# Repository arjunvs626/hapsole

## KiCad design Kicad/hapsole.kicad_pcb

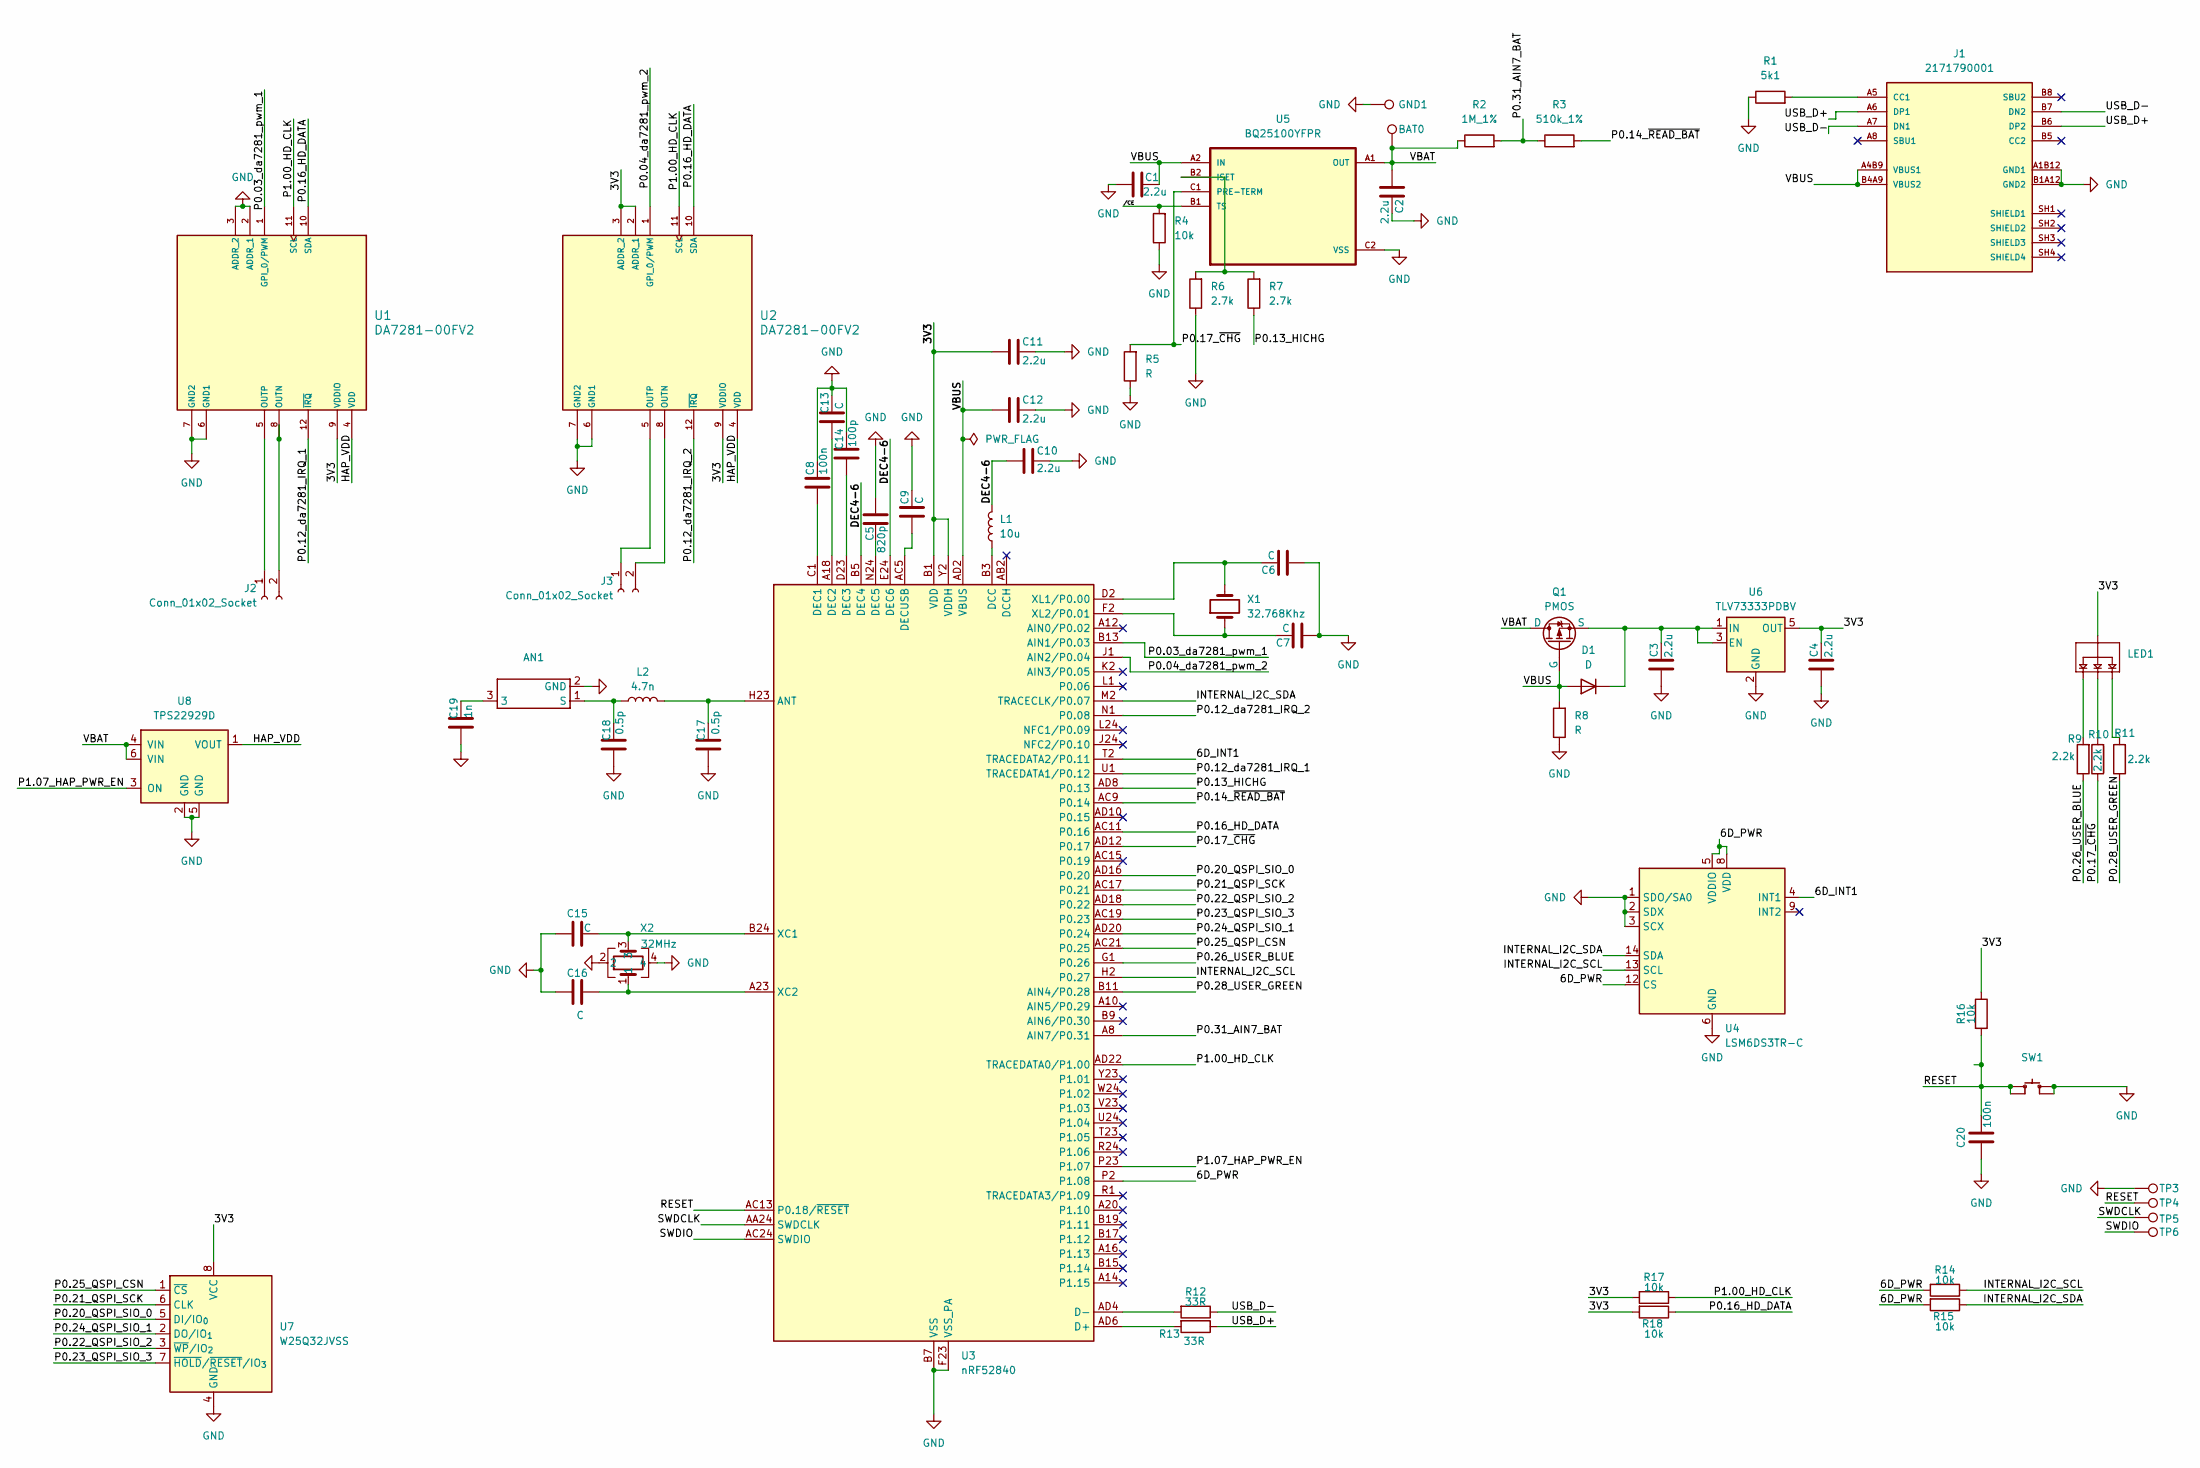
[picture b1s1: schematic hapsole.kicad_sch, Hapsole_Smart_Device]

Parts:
AN1: ANT
C1, C2, C3, C4, C10, C11, C12: 2.2u; C_0201_0603Metric
C5: 820p; C_0201_0603Metric
C6, C7, C9, C13, C15, C16: C; C_0201_0603Metric
C8, C20: 100n; C_0201_0603Metric
C14: 100p; C_0201_0603Metric
C17, C18: 0.5p; C_0201_0603Metric
C19: 1n; C_0201_0603Metric
D1: D; D_0603_1608Metric
J1: 2171790001; MOLEX_2171790001; PARTREV A1; DigiKey_Part_Number 900-2171790001CT-ND
J2, J3: Conn_01x02_Socket; JST_S2B-ZR-SM4A-TF
L1: 10u; L_0402_1005Metric
L2: 4.7n; L_0402_1005Metric
LED1: RGB_LED
Q1: PMOS; SOT-883
R1: 5k1; R_0201_0603Metric
R2: 1M_1%; R_0201_0603Metric
R3: 510k_1%; R_0201_0603Metric
R4, R14, R15, R16, R17, R18: 10k; R_0201_0603Metric
R5, R8: R; R_0201_0603Metric
R6, R7: 2.7k; R_0201_0603Metric
R9, R10, R11: 2.2k; R_0201_0603Metric
R12, R13: 33R; R_0201_0603Metric
SW1: DPST
TP1: BAT0; TestPoint_Pad_D1.5mm
TP2: GND1; TestPoint_Pad_D1.5mm
TP3, TP4, TP5, TP6: TestPoint; TestPoint_Pad_1.0x1.0mm
U1, U2: DA7281-00FV2; DA7281-00FV2_DIL
U3: nRF52840; Nordic_AQFN-73-1EP_7x7mm_P0.5mm
U4: LSM6DS3TR-C; LGA-14_3x2.5mm_P0.5mm_LayoutBorder3x4y
U5: BQ25100YFPR; BGA6N40P3X2_157X88X50N
U6: TLV73333PDBV; SOT-23-5
U7: W25Q32JVSS; Untitled
U8: TPS22929D; SOT-23-6
X1: 32.768Khz; FC135
X2: 32MHz; XC

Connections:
/3V3: C4.2, C11.1, LED1.+, R16.1, R17.2, R18.2, U1.9 (VDDIO), U2.2 (ADDR_1), U2.3 (ADDR_2), U2.9 (VDDIO), U3.A22 (VDD), U3.AD14 (VDD), U3.AD23 (VDD), U3.B1 (VDD), U3.W1 (VDD), U3.Y2 (VDDH), U6.5 (OUT), U7.8 (VCC)
/6D_INT1: U3.T2 (TRACEDATA2/P0.11), U4.4 (INT1)
/6D_PWR: R14.2, R15.2, U3.P2 (P1.08), U4.5 (VDDIO), U4.8 (VDD), U4.12 (CS)
/DEC4-6: C10.1, L1.2, U3.B5 (DEC4), U3.E24 (DEC6)
/HAP_VDD: U1.4 (VDD), U2.4 (VDD), U8.1 (VOUT)
/INTERNAL_I2C_SCL: R14.1, U3.H2 (P0.27), U4.13 (SCL)
/INTERNAL_I2C_SDA: R15.1, U3.M2 (TRACECLK/P0.07), U4.14 (SDA)
/P0.03_da7281_pwm_1: U1.1 (GPI_0/PWM), U3.B13 (AIN1/P0.03)
/P0.04_da7281_pwm_2: U2.1 (GPI_0/PWM), U3.J1 (AIN2/P0.04)
/P0.12_da7281_IRQ_1: U1.12 (~IRQ), U3.U1 (TRACEDATA1/P0.12)
/P0.12_da7281_IRQ_2: U2.12 (~IRQ), U3.N1 (P0.08)
/P0.13_HICHG: R7.1, U3.AD8 (P0.13)
/P0.14_~READ_BAT: R3.2, U3.AC9 (P0.14)
/P0.16_HD_DATA: R18.1, U1.10 (SDA), U2.10 (SDA), U3.AC11 (P0.16)
/P0.17_~CHG: R5.2, R10.1, U3.AD12 (P0.17), U5.C1 (PRE-TERM)
/P0.20_QSPI_SIO_0: U3.AD16 (P0.20), U7.5 (DI/IO_{0})
/P0.21_QSPI_SCK: U3.AC17 (P0.21), U7.6 (CLK)
/P0.22_QSPI_SIO_2: U3.AD18 (P0.22), U7.3 (~WP/IO_{2})
/P0.23_QSPI_SIO_3: U3.AC19 (P0.23), U7.7 (~HOLD/~RESET/IO_{3})
/P0.24_QSPI_SIO_1: U3.AD20 (P0.24), U7.2 (DO/IO_{1})
/P0.25_QSPI_CSN: U3.AC21 (P0.25), U7.1 (~CS)
/P0.26_USER_BLUE: R9.1, U3.G1 (P0.26)
/P0.28_USER_GREEN: R11.1, U3.B11 (AIN4/P0.28)
/P0.31_AIN7_BAT: R2.2, R3.1, U3.A8 (AIN7/P0.31)
/P1.00_HD_CLK: R17.1, U1.11 (SCL), U2.11 (SCL), U3.AD22 (TRACEDATA0/P1.00)
/P1.07_HAP_PWR_EN: U3.P23 (P1.07), U8.3 (ON)
/RESET: C20.1, R16.2, SW1.1 (A0), SW1.3 (A1), TP4.1, U3.AC13 (P0.18/~RESET)
/SWDCLK: TP5.1, U3.AA24 (SWDCLK)
/SWDIO: TP6.1, U3.AC24 (SWDIO)
/USB_D+: J1.A6 (DP1), J1.B6 (DP2), R13.1
/USB_D-: J1.A7 (DN1), J1.B7 (DN2), R12.1
/VBAT: C2.1, Q1.1 (D), R2.1, TP1.1, U5.A1 (OUT), U8.4 (VIN), U8.6 (VIN)
/VBUS: C1.2, C12.1, D1.2 (A), J1.A4B9 (VBUS1), J1.B4A9 (VBUS2), Q1.2 (G), R8.2, U3.AD2 (VBUS), U5.A2 (IN)
//CE: R4.2, U5.B1 (TS)
GND: AN1.2 (GND), C1.1, C2.2, C3.1, C4.1, C5.2, C6.1, C7.1, C8.2, C9.2, C10.2, C11.2, C12.2, C13.2, C14.2, C15.2, C16.2, C17.1, C18.1, C19.1, C20.2, J1.A1B12 (GND1), J1.B1A12 (GND2), R1.1, R4.1, R5.1, R6.1, R8.1, SW1.2 (B0), SW1.4 (B1), TP2.1, TP3.1, U1.2 (ADDR_1), U1.3 (ADDR_2), U1.6 (GND1), U1.7 (GND2), U2.6 (GND1), U2.7 (GND2), U3.B7 (VSS), U3.EP (VSS), U3.F23 (VSS_PA), U4.1 (SDO/SA0), U4.2 (SDX), U4.3 (SCX), U4.6 (GND), U4.7 (GND), U5.C2 (VSS), U6.2 (GND), U7.4 (GND), U8.2 (GND), U8.5 (GND), X2.2, X2.4
unnamed: AN1.3, C19.2
unnamed: AN1.1 (S), C18.2, L2.1
unnamed: C3.2, D1.1 (K), Q1.3 (S), U6.1 (IN), U6.3 (EN)
unnamed: J1.A5 (CC1), R1.2
unnamed: J2.1, U1.5 (OUTP)
unnamed: J2.2, U1.8 (OUTN)
unnamed: J3.1, U2.5 (OUTP)
unnamed: J3.2, U2.8 (OUTN)
unnamed: LED1.B-, R9.2
unnamed: LED1.G-, R10.2
unnamed: LED1.R-, R11.2
unnamed: C17.2, L2.2, U3.H23 (ANT)
unnamed: R13.2, U3.AD6 (D+)
unnamed: R12.2, U3.AD4 (D-)
unnamed: L1.1, U3.B3 (DCC)
unnamed: C8.1, U3.C1 (DEC1)
unnamed: C13.1, U3.A18 (DEC2)
unnamed: C14.1, U3.D23 (DEC3)
unnamed: C5.1, U3.N24 (DEC5)
unnamed: C9.1, U3.AC5 (DECUSB)
unnamed: C15.1, U3.B24 (XC1), X2.3
unnamed: C16.1, U3.A23 (XC2), X2.1
unnamed: C6.2, U3.D2 (XL1/P0.00), X1.2
unnamed: C7.2, U3.F2 (XL2/P0.01), X1.1
unnamed: R6.2, R7.2, U5.B2 (ISET)

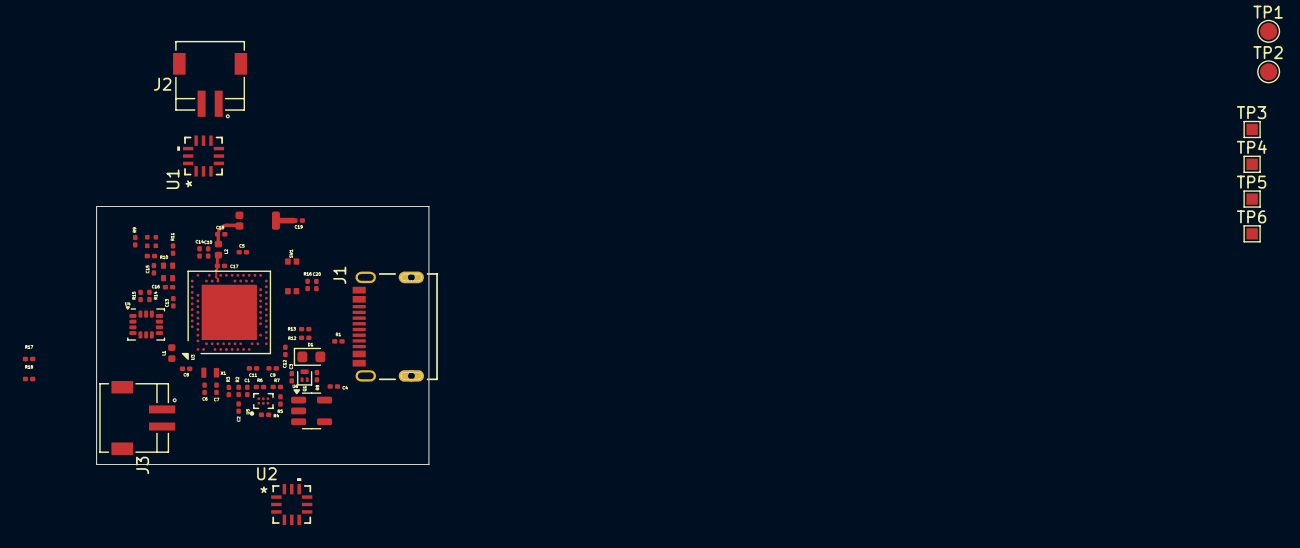
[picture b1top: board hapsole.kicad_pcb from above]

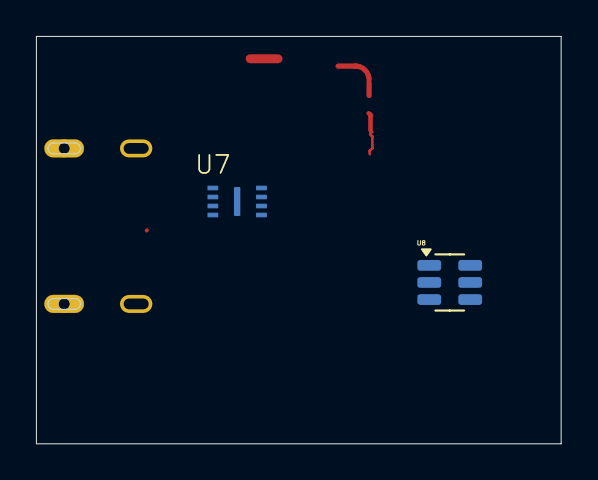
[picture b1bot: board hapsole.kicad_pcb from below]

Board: 4 copper layers, 29.2 x 22.6 mm, 64 parts (2 on the bottom side), 60 nets.

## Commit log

2025-08-07 Intitial Commit for Kicad Project
2025-08-07 Added the crystal
2025-08-07 Organised Folders
2025-08-07 same commit
2025-08-07 Added i2c Pins
2025-08-11 Added MCU Pins TO Do: DA781 implimentation
2025-08-13 added da7281
2025-08-14 Added Footprints of R,C
2025-08-18 initiated the PCB design
2025-08-28 placed the components in PCB & started routing
2025-08-28 added library
2025-08-29 Resized and rearranged components placement
2025-09-09 Deleted the pcb design and start from the scratch
2025-09-11 Arranged the components
2025-09-12 finished arrangement of all components
